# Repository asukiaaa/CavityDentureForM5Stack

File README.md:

# CavityDentureForM5Stack

A kicad project for denture for [CavityForM5Stack](https://github.com/asukiaaa/CavityForM5Stack).

# Usage

Use this project as a template of KiCad to create your original denture.

If you order PCB, 1mm thickness denture will good for CavityForM5Stack.

# License

MIT

# References

- [M5StackのStackに背の高い部品を利用できるM5StackCavityを作ってみた](http://asukiaaa.blogspot.com/2019/08/m5stackstackm5stackcavity.html)
- [KiCadでテンプレートを作って使う方法](http://asukiaaa.blogspot.com/2019/12/kicad-template.html)

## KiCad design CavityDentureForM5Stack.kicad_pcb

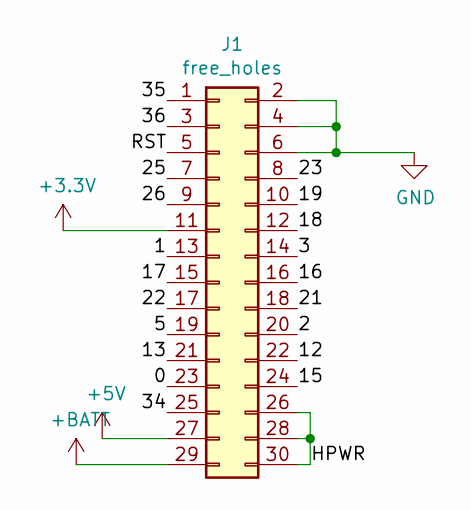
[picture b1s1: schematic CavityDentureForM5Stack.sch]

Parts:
J1: free_holes; Pads_1x30_P1.27mm_Vertical

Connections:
+3V3: J1.11
+5V: J1.27
+BATT: J1.29
/0: J1.23
/1: J1.13
/2: J1.20
/3: J1.14
/5: J1.19
/12: J1.22
/13: J1.21
/15: J1.24
/16: J1.16
/17: J1.15
/18: J1.12
/19: J1.10
/21: J1.18
/22: J1.17
/23: J1.8
/25: J1.7
/26: J1.9
/34: J1.25
/35: J1.1
/36: J1.3
/HPWR: J1.26, J1.28, J1.30
/RST: J1.5
GND: J1.2, J1.4, J1.6

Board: 2 copper layers, 13 parts (0 on the bottom side), 2 nets, no tracks yet.

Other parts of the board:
REF1, REF4, REF6, REF9: MountingHole_3.2mm_M3
REF2, REF3, REF7, REF8: MountingHole_2.2mm_M2
corner1, corner2, corner3, corner4: outer_corner

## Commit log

2019-08-18 Rename project to M5StackCavityDenture
2019-08-18 Add meta for template
2019-08-24 Add sch-bak to gitignore
2019-08-24 Remove redundant components
2019-08-24 Remove unused footprints
2019-08-24 Add image to readme
2019-08-24 Add thickness info to readme
2019-08-24 Add icon for template
2019-08-24 Update info for template
2019-08-24 Add link of M5StackCavity on readme
2019-08-24 Change lang of meta/info.html to en-US from fr-FR
2019-08-24 Update charset of meta/info.html to utf-8 from windows-1252
2019-12-01 Rename project name to CavityDentureForM5Stack
2020-01-04 Add reference links
2020-03-30 Correct label for 35 pin
